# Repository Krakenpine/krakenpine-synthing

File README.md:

# krakenpine-synthing
Synth modules?

I'll keep adding stuff and refine this, but here's something.

Video of the bassdrum module here: https://www.youtube.com/watch?v=iETSEz60OVA

Video of the Kosmo dual VCA module here: https://www.youtube.com/watch?v=iGI92x8AyZQ

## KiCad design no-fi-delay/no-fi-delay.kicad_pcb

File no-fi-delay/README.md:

# No-fi delay v1.0

Very low fidelity delay module in Kosmo format. Uses Arduino Nano 328P version with 2 kB ram.
Install Mozzi library in Arduino IDE to use this.
Files in KiCad format with schematic as pdf.
Jack pcb and main pcb are connected with a 10 pin flat cable, like the one powering eurorack/kosmo modules. Don't accidentally connect power to that connector, otherwise this should be quite straightforward if you have build anything previously.

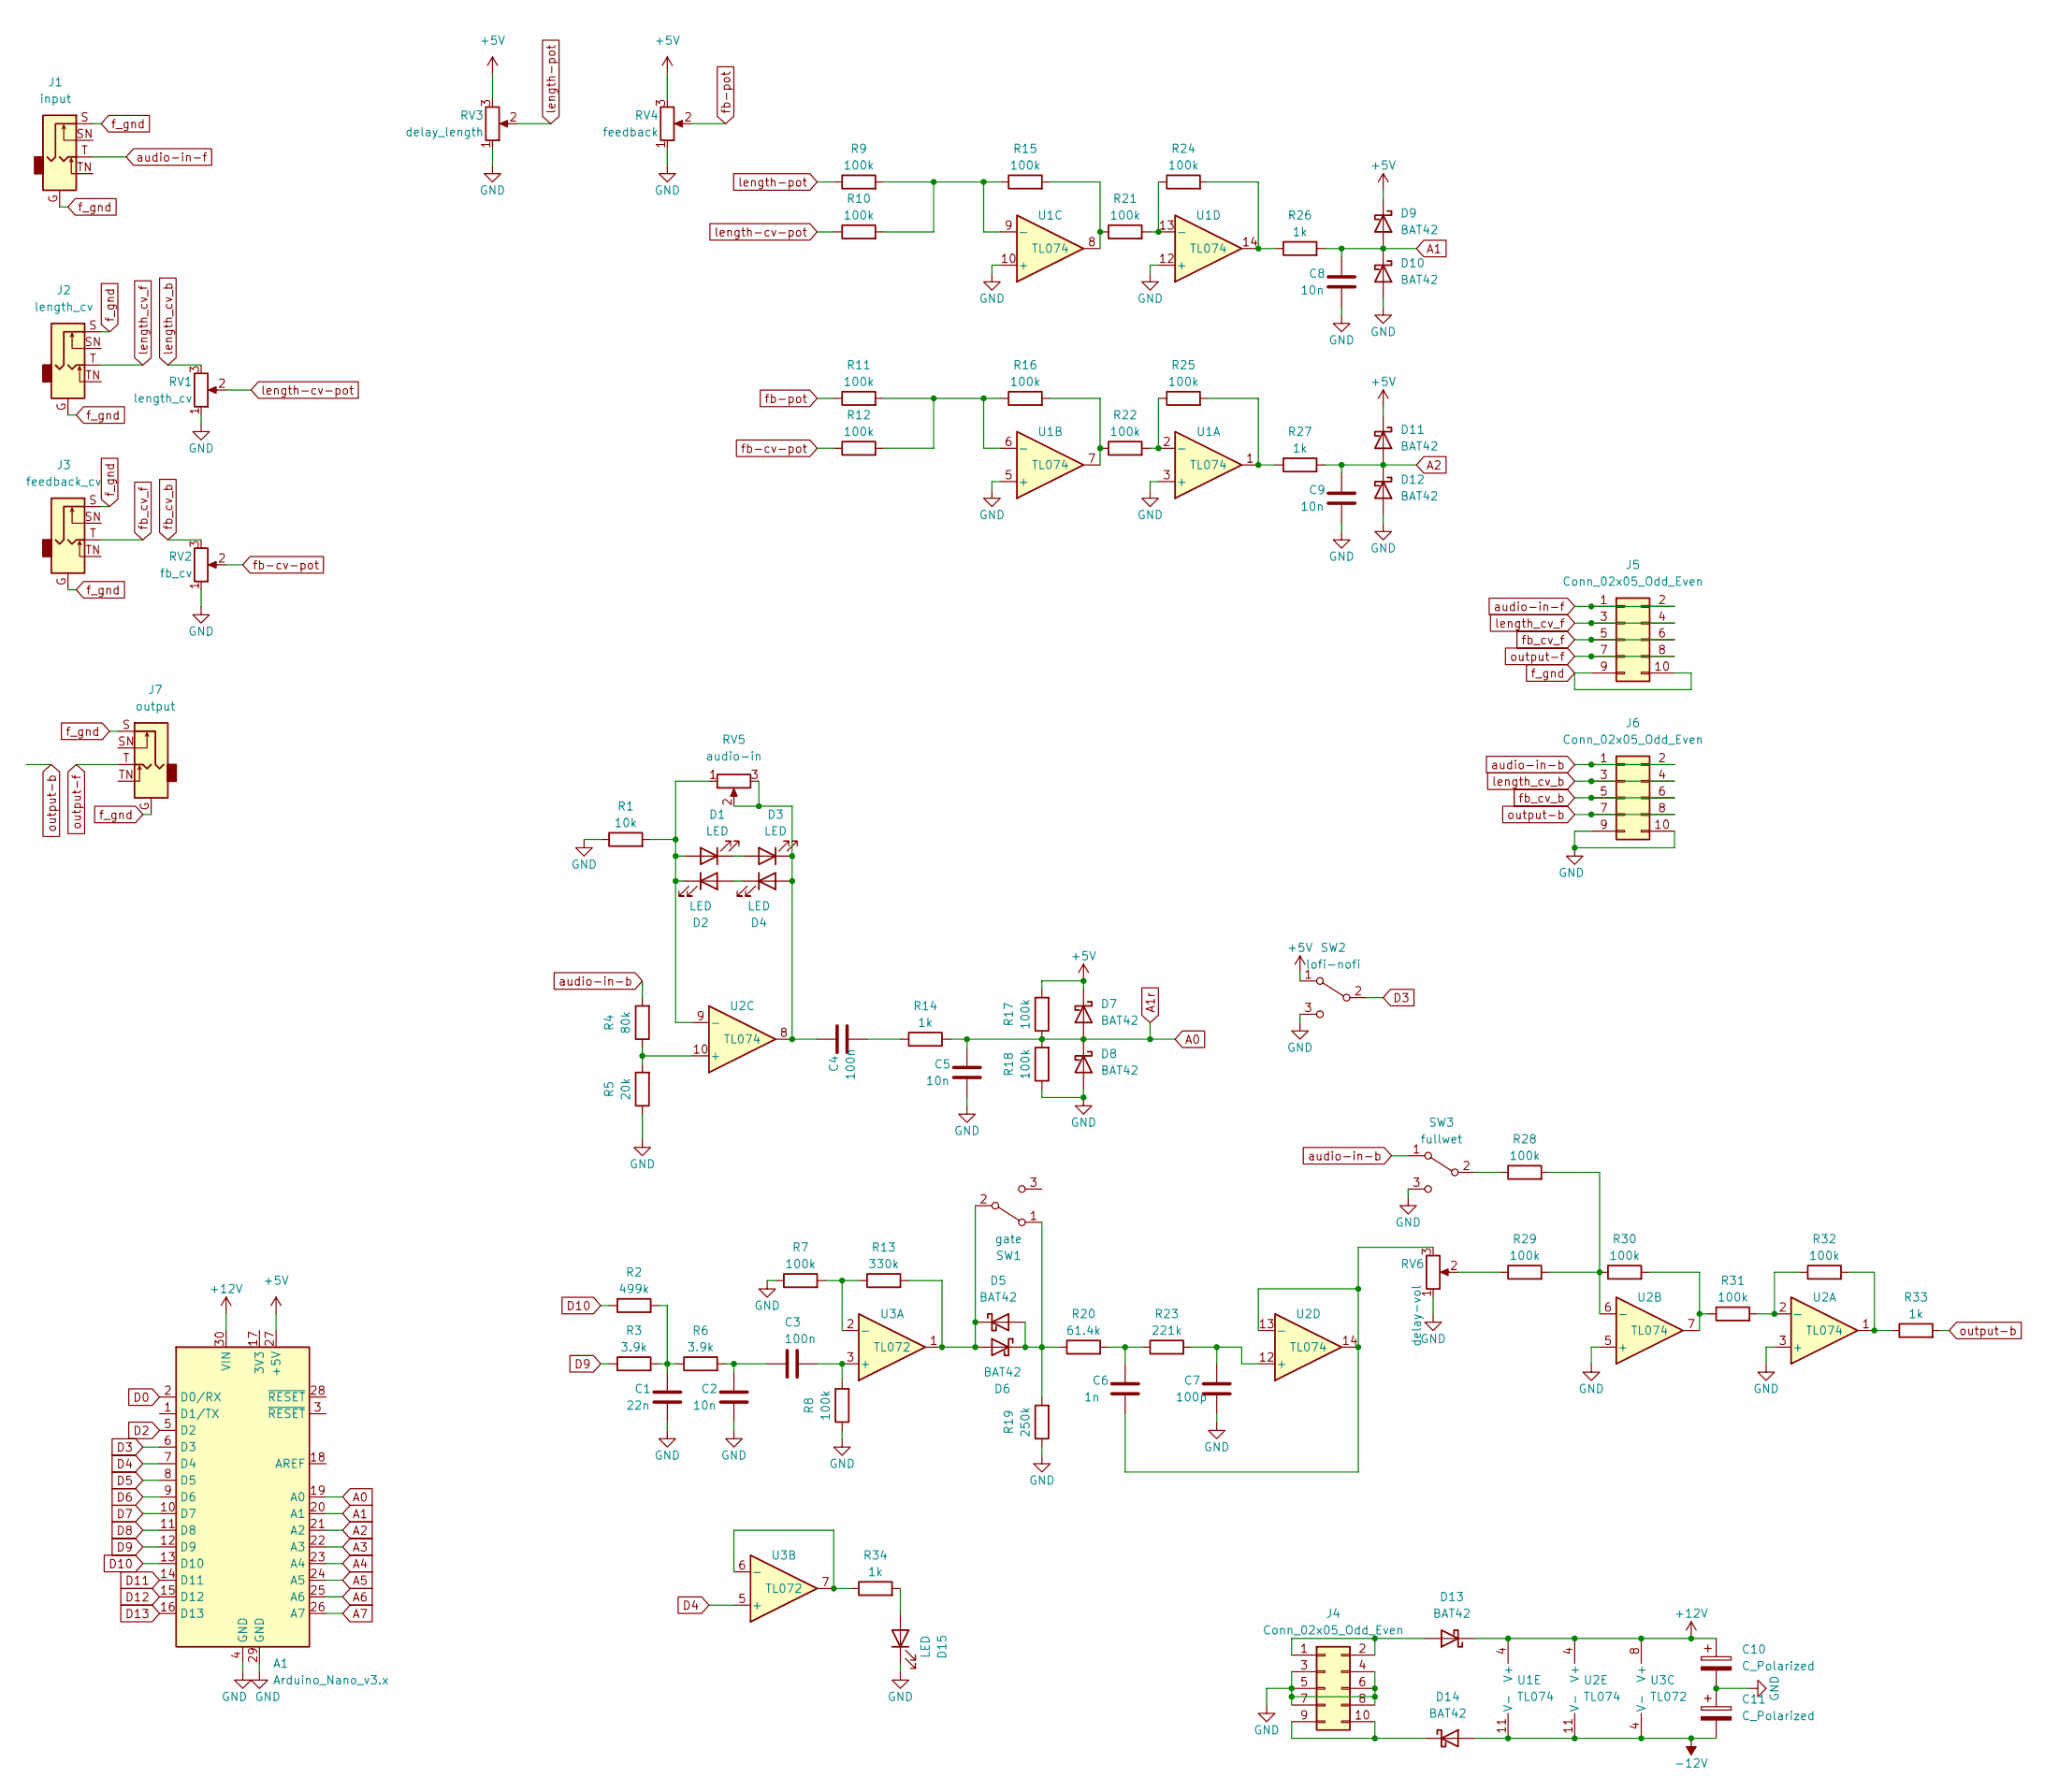
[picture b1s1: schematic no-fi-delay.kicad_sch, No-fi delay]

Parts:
A1: Arduino_Nano_v3.x; Arduino_Nano
C1: 22n; C_Rect_L7.0mm_W2.5mm_P5.00mm
C2, C5, C8, C9: 10n; C_Rect_L7.0mm_W2.5mm_P5.00mm
C3, C4: 100n; C_Rect_L7.0mm_W2.5mm_P5.00mm
C6: 1n; C_Rect_L7.0mm_W2.5mm_P5.00mm
C7: 100p; C_Rect_L7.0mm_W2.5mm_P5.00mm
C10, C11: C_Polarized; CP_Radial_D5.0mm_P2.50mm
D1, D2, D3, D4: LED; LED_D3.0mm
D5, D6, D7, D8, D9, D10, D11, D12, D13, D14: BAT42; D_DO-35_SOD27_P7.62mm_Horizontal
D15: LED; LED_D5.0mm
J1: input; Jack_6.5mm LMNCmid
J2: length_cv; Jack_6.5mm LMNCmid
J3: feedback_cv; Jack_6.5mm LMNCmid
J4, J5, J6: Conn_02x05_Odd_Even; PinHeader_2x05_P2.54mm_Vertical
J7: output; Jack_6.5mm LMNCmid
R1: 10k; Resistor_oma1
R2: 499k; Resistor_oma1
R3, R6: 3.9k; Resistor_oma1
R4: 80k; Resistor_oma1
R5: 20k; Resistor_oma1
R7, R8, R9, R10, R11, R12, R15, R16, R17, R18, R21, R22, R24, R25, R28, R29, R30, R31, R32: 100k; Resistor_oma1
R13: 330k; Resistor_oma1
R14, R26, R27, R33, R34: 1k; Resistor_oma1
R19: 250k; Resistor_oma1
R20: 61.4k; Resistor_oma1
R23: 221k; Resistor_oma1
RV1: length_cv; Potentiometer_Alpha_RD901F-40-00D_Single_Vertical_CircularH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
RV2: fb_cv; Potentiometer_Alpha_RD901F-40-00D_Single_Vertical_CircularH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
RV3: delay_length; Potentiometer_Alpha_RD901F-40-00D_Single_Vertical_CircularH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
RV4: feedback; Potentiometer_Alpha_RD901F-40-00D_Single_Vertical_CircularH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
RV5: audio-in; Potentiometer_Alpha_RD901F-40-00D_Single_Vertical_CircularH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
RV6: delay-vol; Potentiometer_Alpha_RD901F-40-00D_Single_Vertical_CircularH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
SW1: gate; submini switch
SW2: lofi-nofi; submini switch
SW3: fullwet; submini switch
U1, U2: TL074; DIP-14_W7.62mm
U3: TL072; DIP-8_W7.62mm

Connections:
+5V: A1.27 (+5V), D7.1 (K), D9.1 (K), D11.1 (K), R17.2, RV3.3, RV4.3, SW2.1 (A)
+12V: A1.30 (VIN), C10.1, D13.1 (K), U1.4 (V+), U2.4 (V+), U3.8 (V+)
-12V: C11.2, D14.2 (A), U1.11 (V-), U2.11 (V-), U3.4 (V-)
A0: A1.19 (A0), C5.1, D7.2 (A), D8.1 (K), R14.2, R17.1, R18.2
A1: A1.20 (A1), C8.1, D9.2 (A), D10.1 (K), R26.2
A2: A1.21 (A2), C9.1, D11.2 (A), D12.1 (K), R27.2
A3: A1.22 (A3)
A4: A1.23 (A4)
A5: A1.24 (A5)
A6: A1.25 (A6)
A7: A1.26 (A7)
D0: A1.2 (D0/RX)
D2: A1.5 (D2)
D3: A1.6 (D3), SW2.2 (B)
D4: A1.7 (D4), U3.5 (+)
D5: A1.8 (D5)
D6: A1.9 (D6)
D7: A1.10 (D7)
D8: A1.11 (D8)
D9: A1.12 (D9), R3.1
D10: A1.13 (D10), R2.1
D11: A1.14 (D11)
D12: A1.15 (D12)
D13: A1.16 (D13)
GND: A1.4 (GND), A1.29 (GND), C1.2, C2.2, C5.2, C7.2, C8.2, C9.2, C10.2, C11.1, D8.2 (A), D10.2 (A), D12.2 (A), D15.1 (K), J4.3, J4.4, J4.5, J4.6, J4.7, J4.8, J6.9, J6.10, R1.1, R5.1, R7.1, R8.1, R18.1, R19.1, RV1.1, RV2.1, RV3.1, RV4.1, RV6.1, SW2.3 (C), SW3.3 (C), U1.3 (+), U1.5 (+), U1.10 (+), U1.12 (+), U2.3 (+), U2.5 (+)
unnamed: C1.1, R2.2, R3.2, R6.1
unnamed: C2.1, C3.2, R6.2
unnamed: C4.2, R14.1
unnamed: C6.1, R20.2, R23.1
unnamed: D1.2 (A), D2.1 (K), R1.2, RV5.1, U2.9 (-)
unnamed: D1.1 (K), D3.2 (A)
unnamed: D2.2 (A), D4.1 (K)
unnamed: C4.1, D3.1 (K), D4.2 (A), RV5.2, RV5.3, U2.8
unnamed: D5.2 (A), D6.1 (K), R19.2, R20.1, SW1.1 (A)
unnamed: D5.1 (K), D6.2 (A), R13.2, SW1.2 (B), U3.1
unnamed: D13.2 (A), J4.1, J4.2
unnamed: D14.1 (K), J4.9, J4.10
unnamed: D15.2 (A), R34.2
unnamed: R15.2, R21.1, U1.8
unnamed: R16.2, R22.1, U1.7
unnamed: R24.2, R26.1, U1.14
unnamed: R25.2, R27.1, U1.1
unnamed: R29.1, RV6.2
unnamed: R30.2, R31.1, U2.7
unnamed: R32.2, R33.1, U2.1
unnamed: R28.1, SW3.2 (B)
unnamed: R22.2, R25.1, U1.2 (-)
unnamed: R11.2, R12.2, R16.1, U1.6 (-)
unnamed: R9.2, R10.2, R15.1, U1.9 (-)
unnamed: R21.2, R24.1, U1.13 (-)
unnamed: R31.2, R32.1, U2.2 (-)
unnamed: R28.2, R29.2, R30.1, U2.6 (-)
unnamed: R4.1, R5.2, U2.10 (+)
unnamed: C7.1, R23.2, U2.12 (+)
unnamed: C6.2, RV6.3, U2.13 (-), U2.14
unnamed: C3.1, R8.2, U3.3 (+)
unnamed: R7.2, R13.1, U3.2 (-)
unnamed: R34.1, U3.6 (-), U3.7
audio-in-b: J6.1, J6.2, R4.2, SW3.1 (A)
audio-in-f: J1.T, J5.1, J5.2
f_gnd: J1.G, J1.S, J2.G, J2.S, J3.G, J3.S, J5.9, J5.10, J7.G, J7.S
fb-cv-pot: R12.1, RV2.2
fb-pot: R11.1, RV4.2
fb_cv_b: J6.5, J6.6, RV2.3
fb_cv_f: J3.T, J5.5, J5.6
length-cv-pot: R10.1, RV1.2
length-pot: R9.1, RV3.2
length_cv_b: J6.3, J6.4, RV1.3
length_cv_f: J2.T, J5.3, J5.4
output-b: J6.7, J6.8, R33.2
output-f: J5.7, J5.8, J7.T

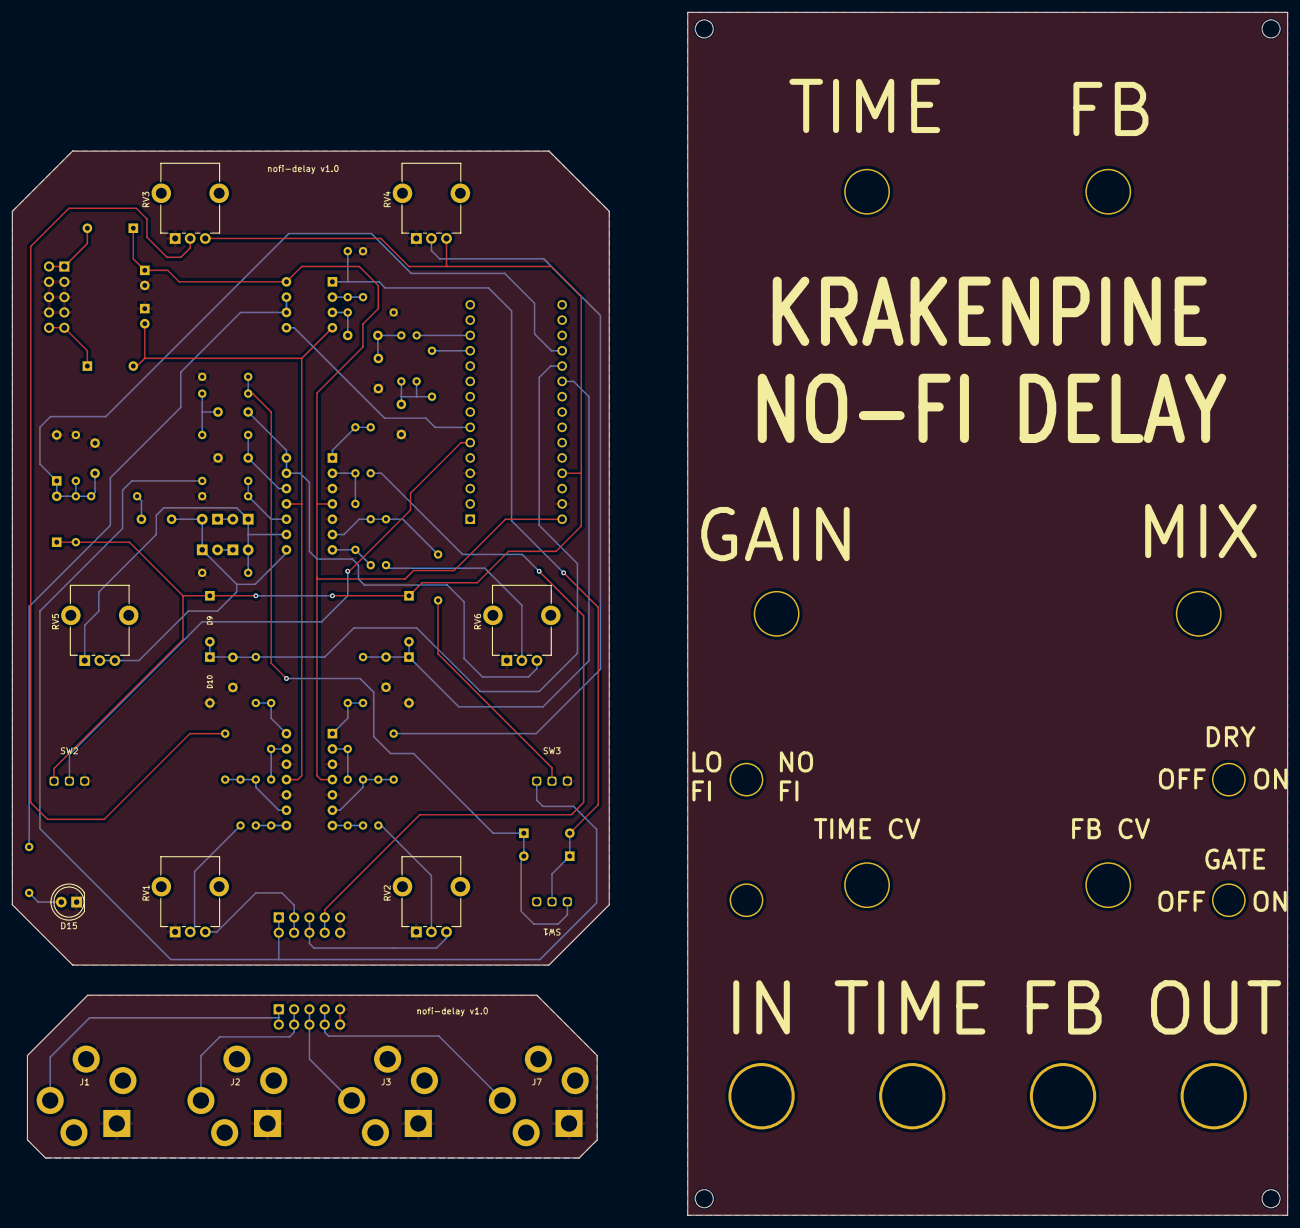
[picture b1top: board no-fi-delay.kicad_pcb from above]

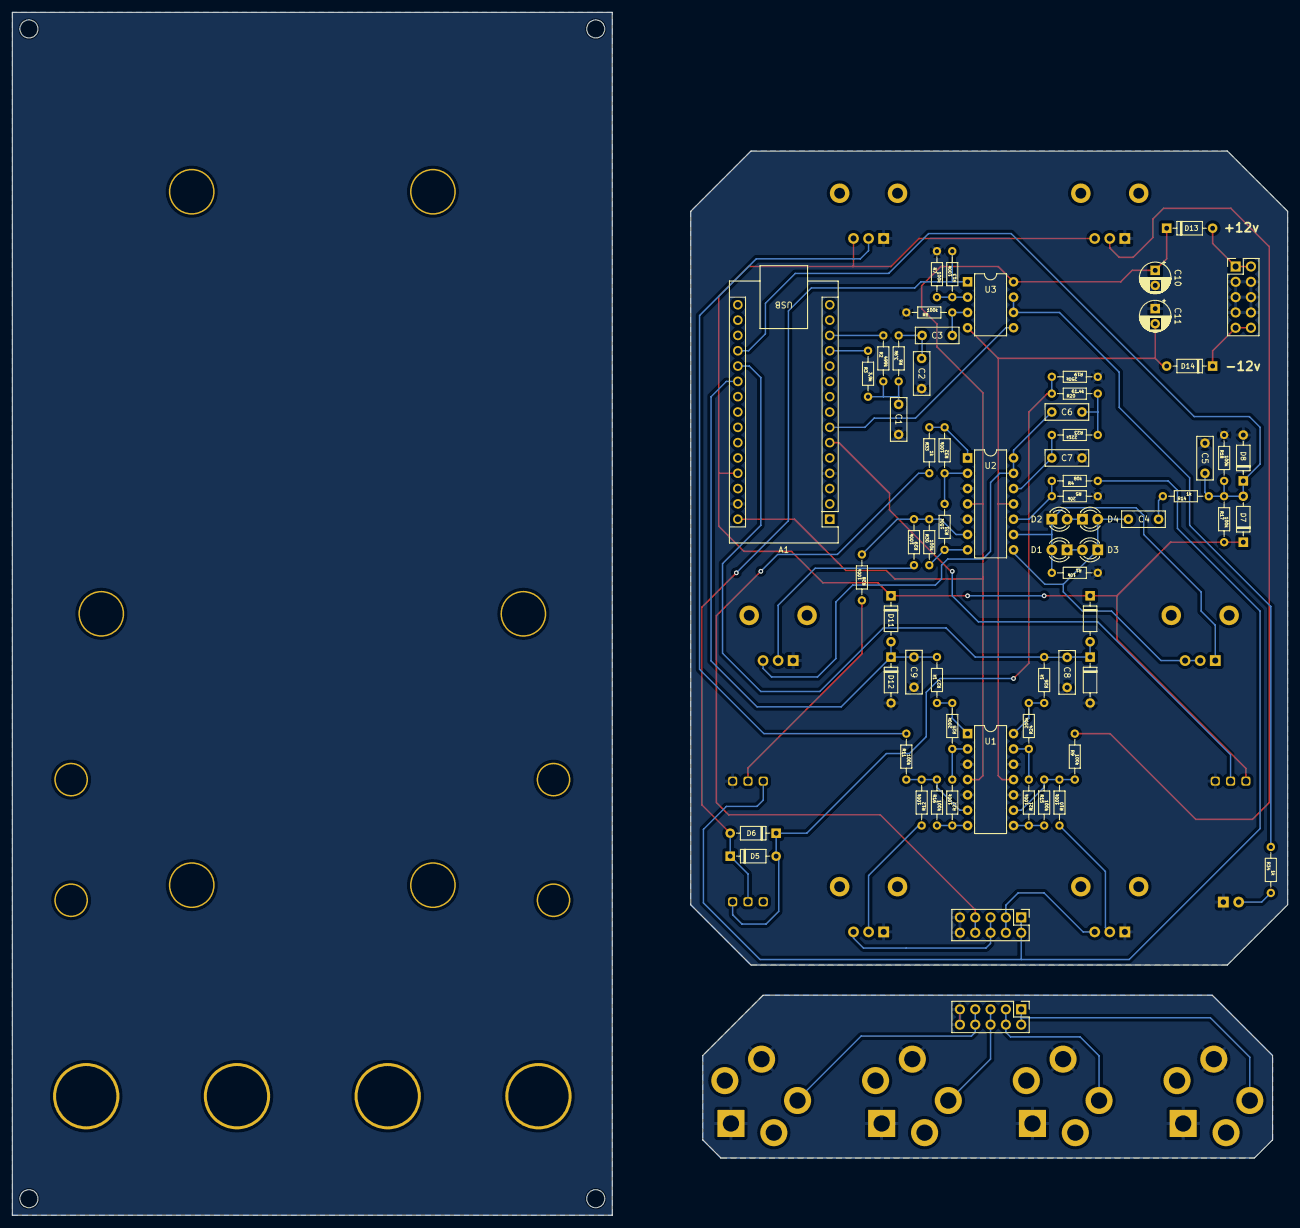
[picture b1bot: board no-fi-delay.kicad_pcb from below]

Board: 2 copper layers, 211.5 x 199.5 mm, 80 parts (66 on the bottom side), 57 nets.

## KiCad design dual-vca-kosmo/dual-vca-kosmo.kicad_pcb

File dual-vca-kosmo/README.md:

# Dual VCA v1.1

Simple dual VCA module in Kosmo format.
Files in KiCad format with schematic as pdf.
Jack pcb and main pcb are connected with a 10 pin flat cable, like the one powering eurorack/kosmo modules. Don't accidentally connect power to that connector, otherwise this should be quite straightforward if you have build anything previously.
This exact version of pcb has not been tested, first version had couple of easily fixable probles that I hopefully fixed also in the kicad file.

V1.1: fixed CV-limiting diode circuit to actually do something

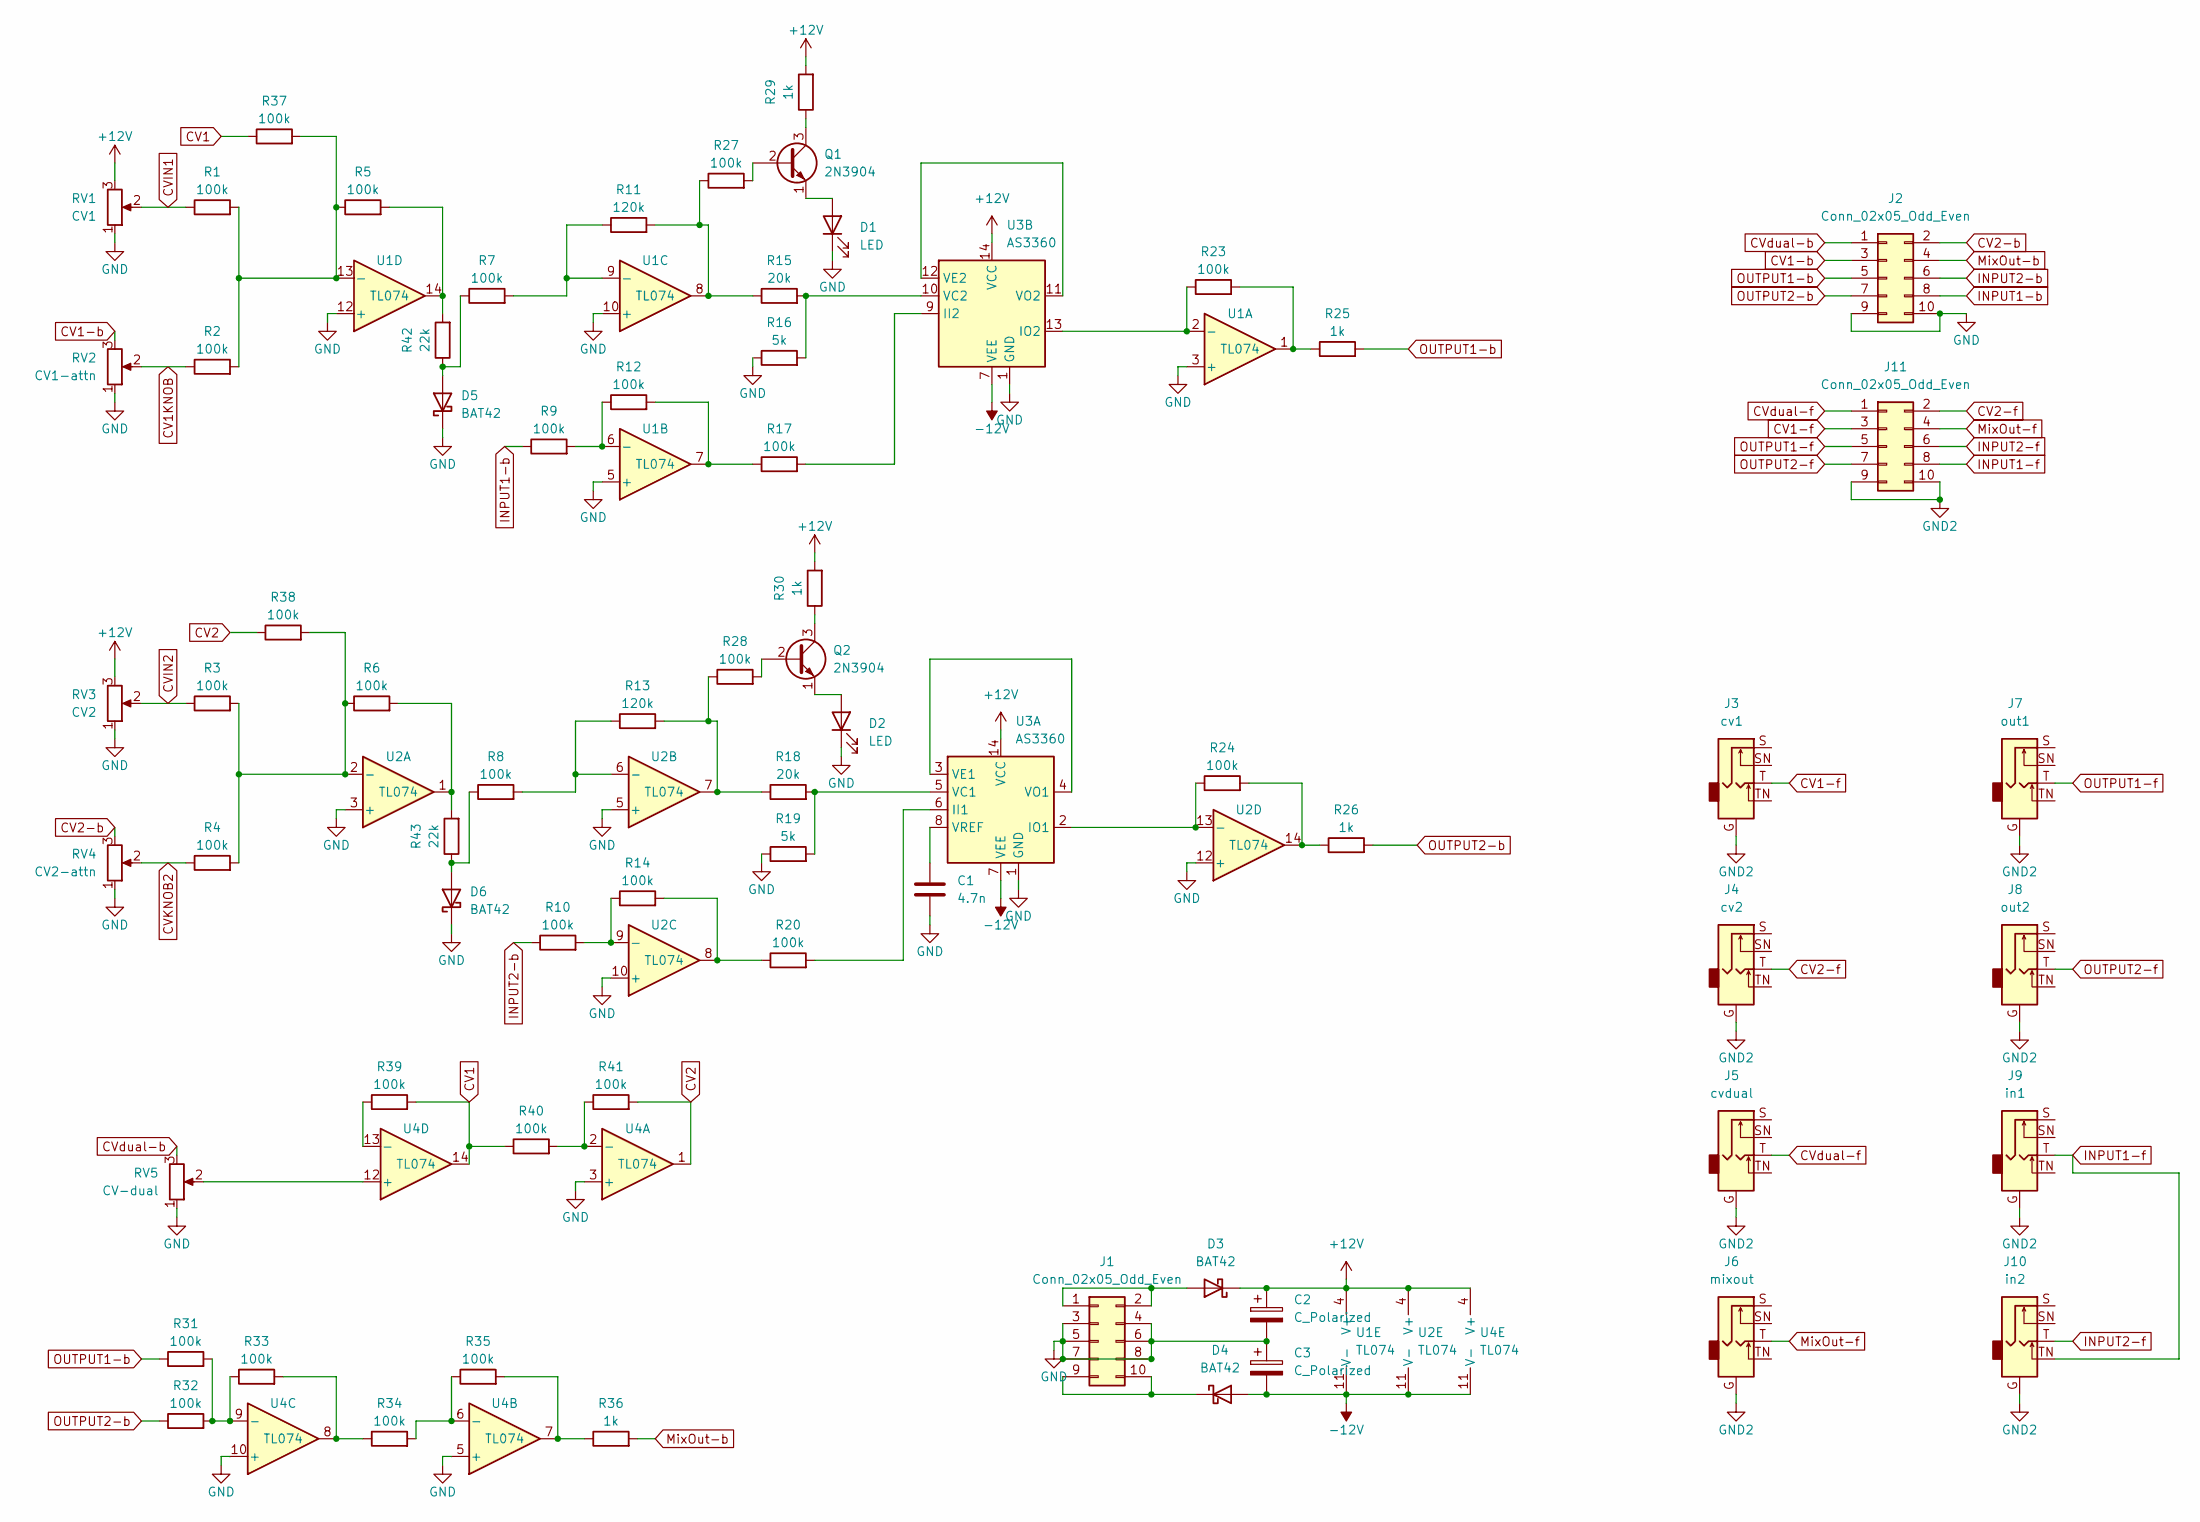
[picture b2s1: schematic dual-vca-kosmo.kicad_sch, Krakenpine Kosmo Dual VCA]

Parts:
C1: 4.7n; C_Disc_D5.0mm_W2.5mm_P5.00mm
C2, C3: C_Polarized; C_Radial_D5.0mm_H7.0mm_P2.00mm
D1, D2: LED; LED_D5.0mm
D3, D4, D5, D6: BAT42; D_DO-35_SOD27_P7.62mm_Horizontal
J1, J2, J11: Conn_02x05_Odd_Even; PinHeader_2x05_P2.54mm_Vertical
J3: cv1; Jack_6.5mm LMNC
J4: cv2; Jack_6.5mm LMNC
J5: cvdual; Jack_6.5mm LMNC
J6: mixout; Jack_6.5mm LMNC
J7: out1; Jack_6.5mm LMNC
J8: out2; Jack_6.5mm LMNC
J9: in1; Jack_6.5mm LMNC
J10: in2; Jack_6.5mm LMNC
Q1, Q2: 2N3904; TO-92_Inline_Wide
R1, R2, R3, R4, R5, R6, R7, R8, R9, R10, R12, R14, R17, R20, R23, R24, R27, R28, R31, R32, R33, R34, R35, R37, R38, R39, R40, R41: 100k; Omaresistor2
R11, R13: 120k; Omaresistor2
R15, R18: 20k; Omaresistor2
R16, R19: 5k; Omaresistor2
R25, R26, R29, R30, R36: 1k; Omaresistor2
R42, R43: 22k; Omaresistor2
RV1: CV1; Potentiometer_Alpha_RD901F-40-00D_Single_Vertical_CircularH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
RV2: CV1-attn; Potentiometer_Alpha_RD901F-40-00D_Single_Vertical_CircularH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
RV3: CV2; Potentiometer_Alpha_RD901F-40-00D_Single_Vertical_CircularH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
RV4: CV2-attn; Potentiometer_Alpha_RD901F-40-00D_Single_Vertical_CircularH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
RV5: CV-dual; Potentiometer_Alpha_RD901F-40-00D_Single_Vertical_CircularH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
U1, U2, U4: TL074; DIP-14_W7.62mm
U3: AS3360; DIP-14_W7.62mm

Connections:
+12V: C2.1, D3.1 (K), R29.2, R30.2, RV1.3, RV3.3, U1.4 (V+), U2.4 (V+), U3.14 (VCC), U4.4 (V+)
-12V: C3.2, D4.2 (A), U1.11 (V-), U2.11 (V-), U3.7 (VEE), U4.11 (V-)
CV1: R37.1, R39.2, R40.1, U4.14
CV1-b: J2.3, RV2.3
CV1-f: J3.T, J11.3
CV1KNOB: R2.1, RV2.2
CV2: R38.1, R41.2, U4.1
CV2-b: J2.2, RV4.3
CV2-f: J4.T, J11.2
CVIN1: R1.1, RV1.2
CVIN2: R3.1, RV3.2
CVKNOB2: R4.1, RV4.2
CVdual-b: J2.1, RV5.3
CVdual-f: J5.T, J11.1
GND: C1.2, C2.2, C3.1, D1.1 (K), D2.1 (K), D5.1 (K), D6.1 (K), J1.3, J1.4, J1.5, J1.6, J1.7, J1.8, J2.9, J2.10, R16.1, R19.1, RV1.1, RV2.1, RV3.1, RV4.1, RV5.1, U1.3 (+), U1.5 (+), U1.10 (+), U1.12 (+), U2.3 (+), U2.5 (+), U2.10 (+), U2.12 (+), U3.1 (GND), U4.3 (+), U4.5 (+), U4.10 (+)
GND2: J3.G, J4.G, J5.G, J6.G, J7.G, J8.G, J9.G, J10.G, J11.9, J11.10
INPUT1-b: J2.8, R9.1
INPUT1-f: J9.T, J10.TN, J11.8
INPUT2-b: J2.6, R10.1
INPUT2-f: J10.T, J11.6
MixOut-b: J2.4, R36.2
MixOut-f: J6.T, J11.4
unnamed: D1.2 (A), Q1.1 (E)
unnamed: D2.2 (A), Q2.1 (E)
unnamed: D3.2 (A), J1.1, J1.2
unnamed: D4.1 (K), J1.9, J1.10
unnamed: D5.2 (A), R7.1, R42.1
unnamed: D6.2 (A), R8.1, R43.1
unnamed: Q1.2 (B), R27.2
unnamed: Q1.3 (C), R29.1
unnamed: Q2.2 (B), R28.2
unnamed: Q2.3 (C), R30.1
unnamed: R11.2, R15.1, R27.1, U1.8
unnamed: R12.2, R17.1, U1.7
unnamed: R13.2, R18.1, R28.1, U2.7
unnamed: R14.2, R20.1, U2.8
unnamed: R23.2, R25.1, U1.1
unnamed: R24.2, R26.1, U2.14
unnamed: R33.2, R34.1, U4.8
unnamed: R35.2, R36.1, U4.7
unnamed: R5.2, R42.2, U1.14
unnamed: R6.2, R43.2, U2.1
unnamed: R23.1, U1.2 (-), U3.13 (IO2)
unnamed: R9.2, R12.1, U1.6 (-)
unnamed: R7.2, R11.1, U1.9 (-)
unnamed: R1.2, R2.2, R5.1, R37.2, U1.13 (-)
unnamed: R3.2, R4.2, R6.1, R38.2, U2.2 (-)
unnamed: R8.2, R13.1, U2.6 (-)
unnamed: R10.2, R14.1, U2.9 (-)
unnamed: R24.1, U2.13 (-), U3.2 (IO1)
unnamed: R20.2, U3.6 (II1)
unnamed: R18.2, R19.2, U3.5 (VC1)
unnamed: U3.3 (VE1), U3.4 (VO1)
unnamed: C1.1, U3.8 (VREF)
unnamed: R17.2, U3.9 (II2)
unnamed: R15.2, R16.2, U3.10 (VC2)
unnamed: U3.11 (VO2), U3.12 (VE2)
unnamed: R40.2, R41.1, U4.2 (-)
unnamed: R34.2, R35.1, U4.6 (-)
unnamed: R31.2, R32.2, R33.1, U4.9 (-)
unnamed: RV5.2, U4.12 (+)
unnamed: R39.1, U4.13 (-)
OUTPUT1-b: J2.5, R25.2, R31.1
OUTPUT1-f: J7.T, J11.5
OUTPUT2-b: J2.7, R26.2, R32.1
OUTPUT2-f: J8.T, J11.7

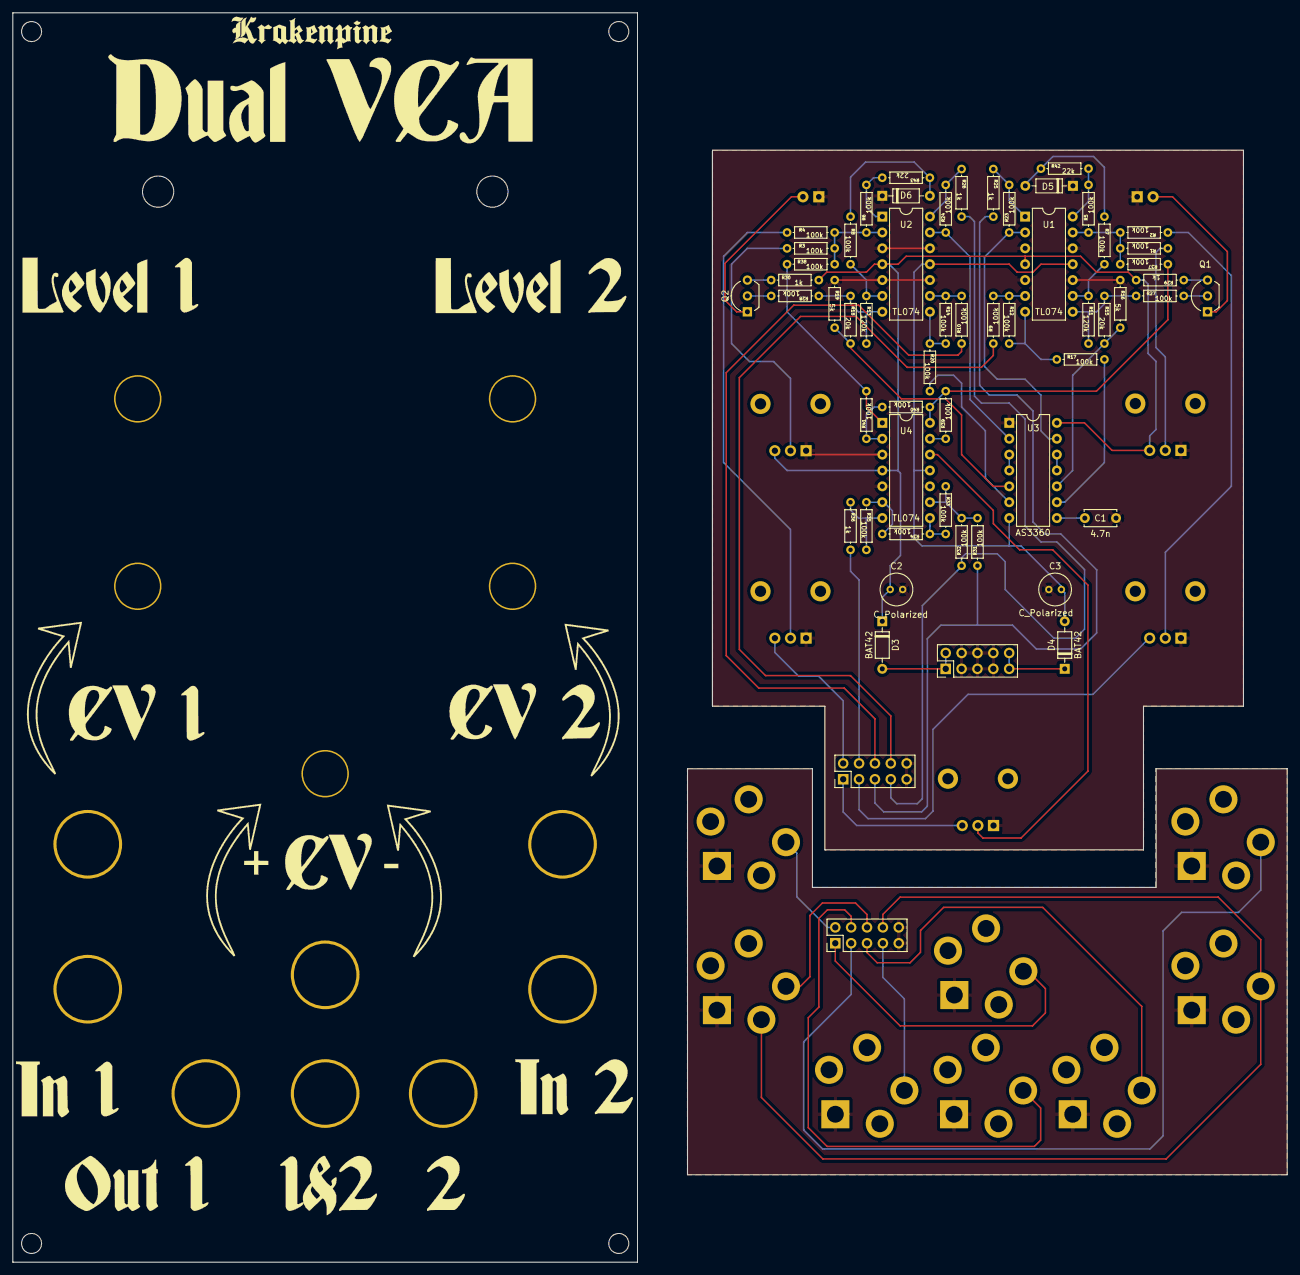
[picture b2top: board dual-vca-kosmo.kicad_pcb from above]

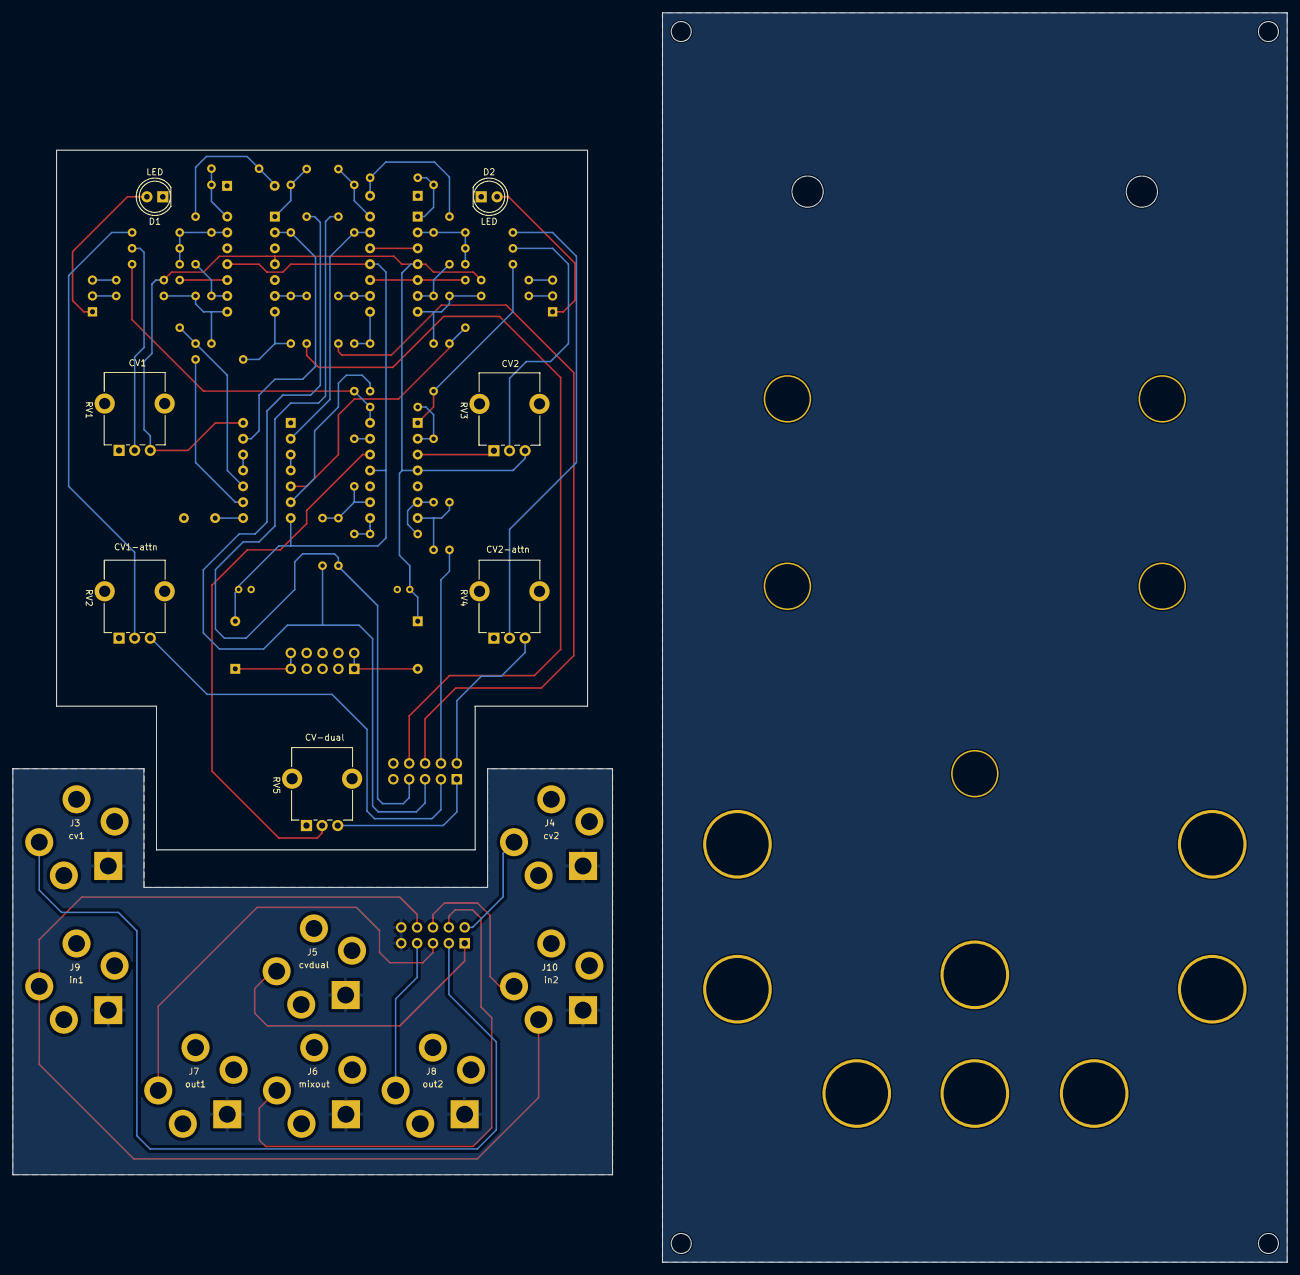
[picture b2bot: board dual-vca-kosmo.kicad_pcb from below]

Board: 2 copper layers, 204.0 x 200.0 mm, 73 parts (15 on the bottom side), 66 nets.

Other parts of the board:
Ref**: Val**; dvca1

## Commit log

2021-02-04 Added bassdrum schematic
2021-03-12 Create dual-release-schematic.png
    Dual release enveloper generator schematic
2021-06-01 Create wavefolder-schematic.png
    Wavefolder schematic
2024-09-22 Kosmo dual vca v1.0
2024-09-22 Actually update schematic to V1.0
2024-09-22 VCA video to readme
2024-09-24 Schematic V1.1, fixed CV limiting
2024-09-26 Updated readme to v1.1
2024-09-26 Updated schematic pdf to v1.1
2024-12-09 no-fi delay v1.0
